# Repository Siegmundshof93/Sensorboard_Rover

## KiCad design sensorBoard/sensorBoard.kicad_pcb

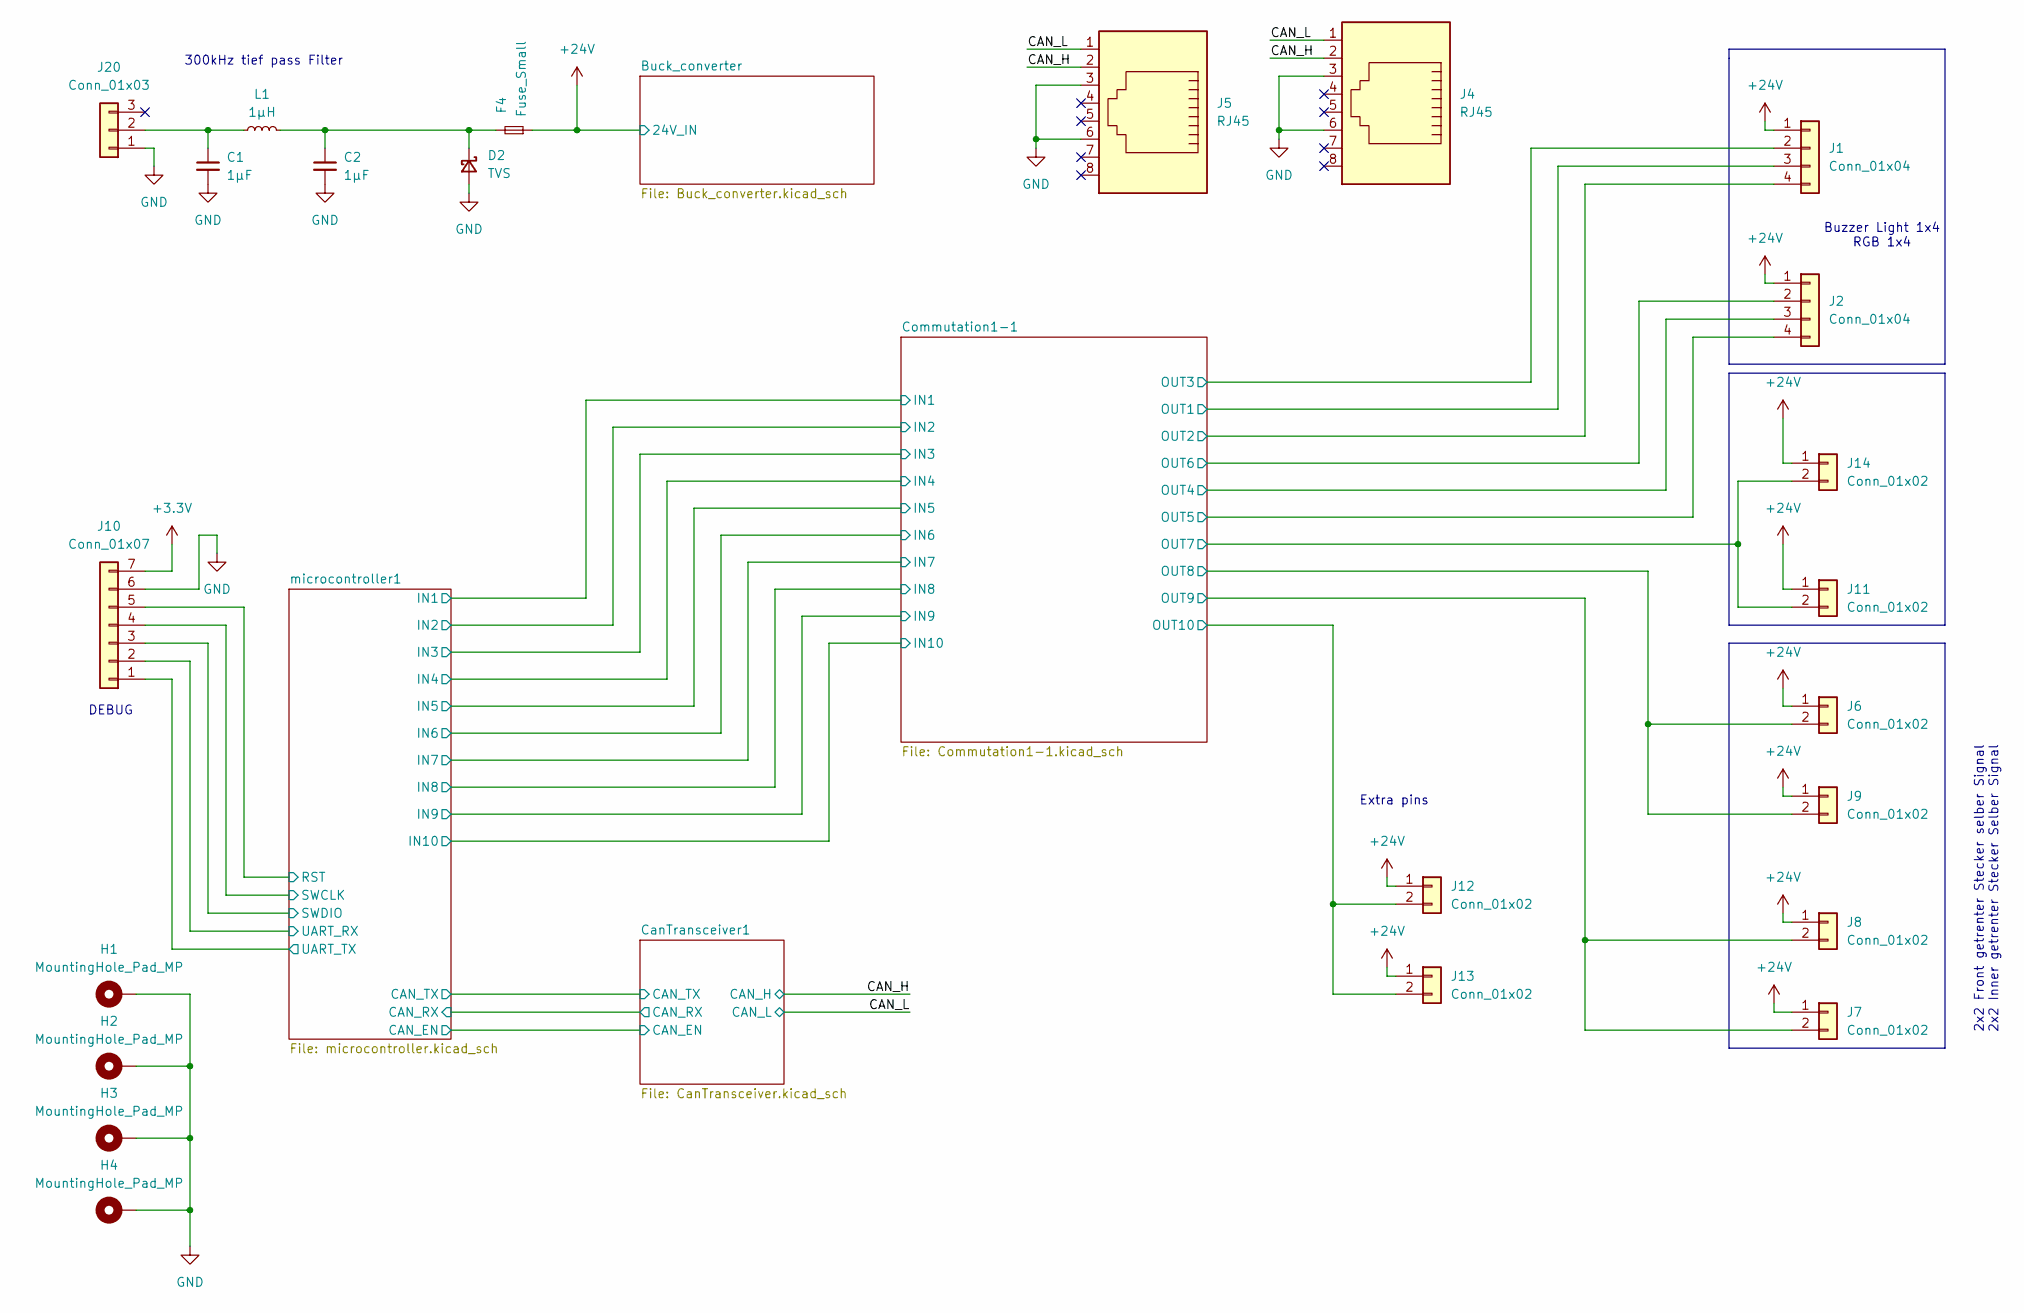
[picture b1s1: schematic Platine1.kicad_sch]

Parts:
C1, C2: 1µF; C_0603_1608Metric
D2: TVS; D_SOD-323
F4: Fuse_Small; Fuse_1206_3216Metric
H1, H2, H3, H4: MountingHole_Pad_MP; MountingHole_2.5mm_Pad_Via
J1, J2: Conn_01x04; J_Wurth_WR-MPC3_662004231722
J4, J5: RJ45; RJ45_Amphenol_RJHSE5380
J6, J7, J8, J9, J12, J13: Conn_01x02; J_Wurth_WR-MPC3_662102145021
J10: Conn_01x07; PinHeader_1x07_P2.54mm_Vertical
J11, J14: Conn_01x02; J_Wurth_WR-MPC3_662002231722
J20: Conn_01x03; Untitled
L1: 1µH; L_Wuerth_WE-PD-Typ-7345

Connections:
+3.3V: J10.7; also elsewhere on the board
+24V: F4.1, J1.1, J2.1, J6.1, J7.1, J8.1, J9.1, J11.1, J12.1, J13.1, J14.1; also elsewhere on the board
/Platine1/CAN_H: J4.2, J5.2; also elsewhere on the board
/Platine1/CAN_L: J4.1, J5.1; also elsewhere on the board
/Platine1/Commutation1-1/OUT1: J1.3; also elsewhere on the board
/Platine1/Commutation1-1/OUT2: J1.4; also elsewhere on the board
/Platine1/Commutation1-1/OUT3: J1.2; also elsewhere on the board
/Platine1/Commutation1-1/OUT4: J2.3; also elsewhere on the board
/Platine1/Commutation1-1/OUT5: J2.4; also elsewhere on the board
/Platine1/Commutation1-1/OUT6: J2.2; also elsewhere on the board
/Platine1/Commutation1-1/OUT7: J11.2, J14.2; also elsewhere on the board
/Platine1/Commutation1-1/OUT8: J6.2, J9.2; also elsewhere on the board
/Platine1/Commutation1-1/OUT9: J7.2, J8.2; also elsewhere on the board
/Platine1/Commutation1-1/OUT10: J12.2, J13.2; also elsewhere on the board
/Platine1/microcontroller1/RST: J10.5; also elsewhere on the board
/Platine1/microcontroller1/SWCLK: J10.4; also elsewhere on the board
/Platine1/microcontroller1/SWDIO: J10.3; also elsewhere on the board
/Platine1/microcontroller1/UART_RX: J10.2; also elsewhere on the board
/Platine1/microcontroller1/UART_TX: J10.1; also elsewhere on the board
GND: C1.2, C2.2, D2.2 (A), H1.MP, H2.MP, H3.MP, H4.MP, J4.3, J4.6, J5.3, J5.6, J10.6, J20.1; also elsewhere on the board
unnamed: C2.1, D2.1 (K), F4.2, L1.2
unnamed: C1.1, J20.2, L1.1

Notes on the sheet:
DEBUG
Buzzer Light 1x4 RGB 1x4
Extra pins
2x2 Front getrenter Stecker selber Signal 2x2 Inner getrenter Stecker Selber Signal
300kHz tief pass Filter

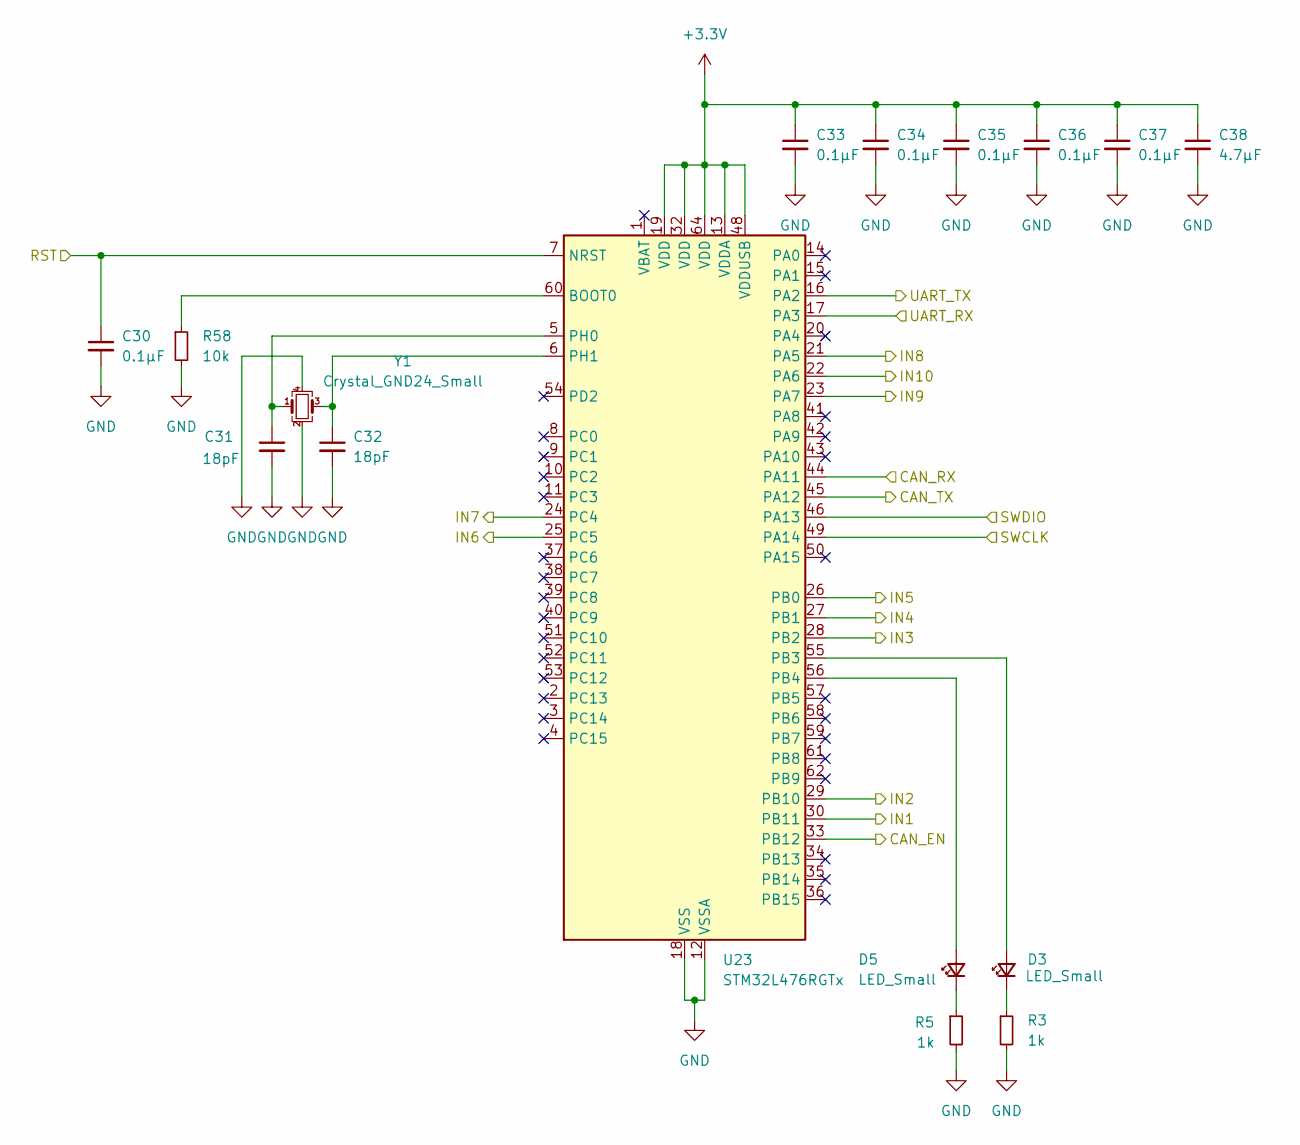
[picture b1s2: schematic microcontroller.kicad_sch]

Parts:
C30, C33, C34, C35, C36, C37: 0.1µF; C_0805_2012Metric
C31, C32: 18pF; C_0805_2012Metric
C38: 4.7µF; C_0805_2012Metric
D3, D5: LED_Small; LED_0805_2012Metric
R3, R5: 1k; R_0805_2012Metric
R58: 10k; R_0805_2012Metric
U23: STM32L476RGTx; LQFP-64_10x10mm_P0.5mm
Y1: Crystal_GND24_Small; Crystal_SMD_3225-4Pin_3.2x2.5mm

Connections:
+3.3V: C33.1, C34.1, C35.1, C36.1, C37.1, C38.1, U23.13 (VDDA), U23.19 (VDD), U23.32 (VDD), U23.48 (VDDUSB), U23.64 (VDD); also elsewhere on the board
/Platine1/CanTransceiver1/CAN_RX: U23.44 (PA11); also elsewhere on the board
/Platine1/CanTransceiver1/CAN_TX: U23.45 (PA12); also elsewhere on the board
/Platine1/Commutation1-1/IN1: U23.30 (PB11); also elsewhere on the board
/Platine1/Commutation1-1/IN2: U23.29 (PB10); also elsewhere on the board
/Platine1/Commutation1-1/IN3: U23.28 (PB2); also elsewhere on the board
/Platine1/Commutation1-1/IN4: U23.27 (PB1); also elsewhere on the board
/Platine1/Commutation1-1/IN5: U23.26 (PB0); also elsewhere on the board
/Platine1/Commutation1-1/IN6: U23.25 (PC5); also elsewhere on the board
/Platine1/Commutation1-1/IN7: U23.24 (PC4); also elsewhere on the board
/Platine1/Commutation1-1/IN8: U23.21 (PA5); also elsewhere on the board
/Platine1/Commutation1-1/IN9: U23.23 (PA7); also elsewhere on the board
/Platine1/Commutation1-1/IN10: U23.22 (PA6); also elsewhere on the board
/Platine1/microcontroller1/CAN_EN: U23.33 (PB12)
/Platine1/microcontroller1/RST: C30.1, U23.7 (NRST); also elsewhere on the board
/Platine1/microcontroller1/SWCLK: U23.49 (PA14); also elsewhere on the board
/Platine1/microcontroller1/SWDIO: U23.46 (PA13); also elsewhere on the board
/Platine1/microcontroller1/UART_RX: U23.17 (PA3); also elsewhere on the board
/Platine1/microcontroller1/UART_TX: U23.16 (PA2); also elsewhere on the board
GND: C30.2, C31.2, C32.2, C33.2, C34.2, C35.2, C36.2, C37.2, C38.2, R3.2, R5.2, R58.2, U23.12 (VSSA), U23.18 (VSS), U23.31 (VSS), U23.47 (VSS), U23.63 (VSS), Y1.2, Y1.4; also elsewhere on the board
unnamed: D3.2 (A), U23.55 (PB3)
unnamed: D3.1 (K), R3.1
unnamed: D5.2 (A), U23.56 (PB4)
unnamed: D5.1 (K), R5.1
unnamed: R58.1, U23.60 (BOOT0)
unnamed: C31.1, U23.5 (PH0), Y1.1
unnamed: C32.1, U23.6 (PH1), Y1.3

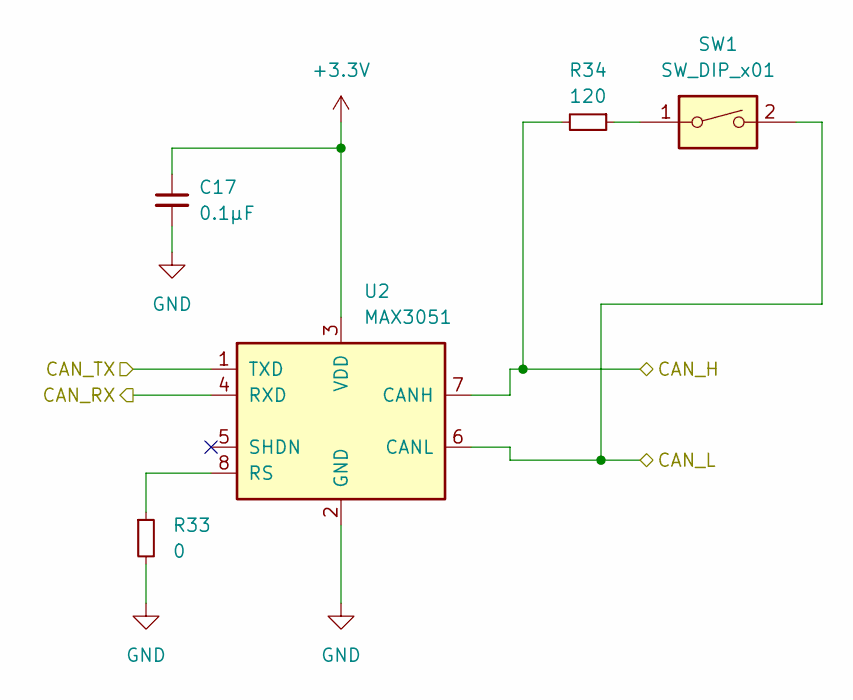
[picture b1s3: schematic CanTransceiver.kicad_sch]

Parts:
C17: 0.1µF; C_0805_2012Metric
R33: 0; R_0805_2012Metric
R34: 120; R_0805_2012Metric
SW1: SW_DIP_x01; 416131160801
U2: MAX3051; SOIC-8_3.9x4.9mm_P1.27mm

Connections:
+3.3V: C17.1, U2.3 (VDD); also elsewhere on the board
/Platine1/CAN_H: R34.2, U2.7 (CANH); also elsewhere on the board
/Platine1/CAN_L: SW1.2, U2.6 (CANL); also elsewhere on the board
/Platine1/CanTransceiver1/CAN_RX: U2.4 (RXD); also elsewhere on the board
/Platine1/CanTransceiver1/CAN_TX: U2.1 (TXD); also elsewhere on the board
GND: C17.2, R33.2, U2.2 (GND); also elsewhere on the board
unnamed: R34.1, SW1.1
unnamed: R33.1, U2.8 (RS)

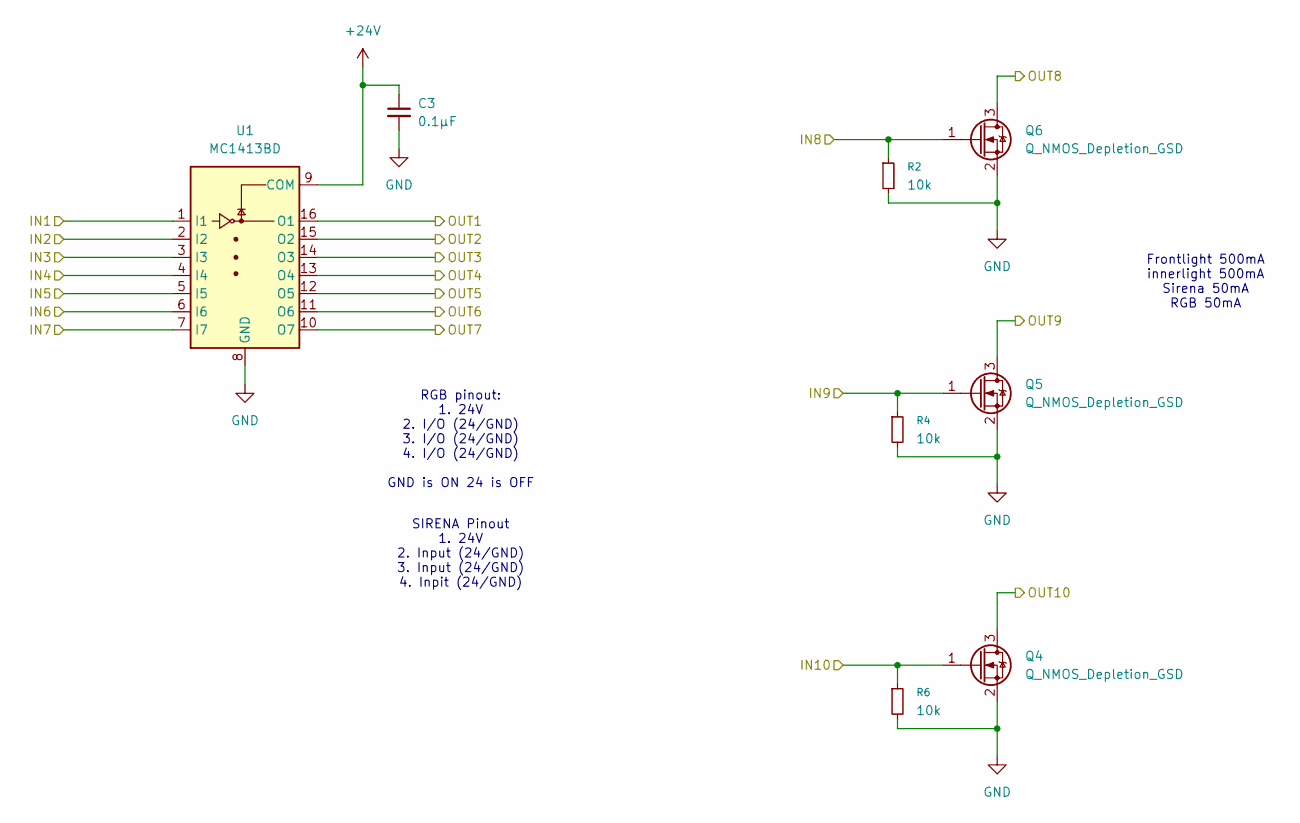
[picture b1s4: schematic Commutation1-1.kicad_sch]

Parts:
C3: 0.1µF; C_0603_1608Metric
Q4, Q5, Q6: Q_NMOS_Depletion_GSD; SOT-23
R2, R4, R6: 10k; R_0805_2012Metric
U1: MC1413BD; SOIC-16_3.9x9.9mm_P1.27mm

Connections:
+24V: C3.1, U1.9 (COM); also elsewhere on the board
/Platine1/Commutation1-1/IN1: U1.1 (I1); also elsewhere on the board
/Platine1/Commutation1-1/IN2: U1.2 (I2); also elsewhere on the board
/Platine1/Commutation1-1/IN3: U1.3 (I3); also elsewhere on the board
/Platine1/Commutation1-1/IN4: U1.4 (I4); also elsewhere on the board
/Platine1/Commutation1-1/IN5: U1.5 (I5); also elsewhere on the board
/Platine1/Commutation1-1/IN6: U1.6 (I6); also elsewhere on the board
/Platine1/Commutation1-1/IN7: U1.7 (I7); also elsewhere on the board
/Platine1/Commutation1-1/IN8: Q6.1 (G), R2.1; also elsewhere on the board
/Platine1/Commutation1-1/IN9: Q5.1 (G), R4.1; also elsewhere on the board
/Platine1/Commutation1-1/IN10: Q4.1 (G), R6.1; also elsewhere on the board
/Platine1/Commutation1-1/OUT1: U1.16 (O1); also elsewhere on the board
/Platine1/Commutation1-1/OUT2: U1.15 (O2); also elsewhere on the board
/Platine1/Commutation1-1/OUT3: U1.14 (O3); also elsewhere on the board
/Platine1/Commutation1-1/OUT4: U1.13 (O4); also elsewhere on the board
/Platine1/Commutation1-1/OUT5: U1.12 (O5); also elsewhere on the board
/Platine1/Commutation1-1/OUT6: U1.11 (O6); also elsewhere on the board
/Platine1/Commutation1-1/OUT7: U1.10 (O7); also elsewhere on the board
/Platine1/Commutation1-1/OUT8: Q6.3 (D); also elsewhere on the board
/Platine1/Commutation1-1/OUT9: Q5.3 (D); also elsewhere on the board
/Platine1/Commutation1-1/OUT10: Q4.3 (D); also elsewhere on the board
GND: C3.2, Q4.2 (S), Q5.2 (S), Q6.2 (S), R2.2, R4.2, R6.2, U1.8 (GND); also elsewhere on the board

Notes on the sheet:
RGB pinout: 1. 24V 2. I/O (24/GND) 3. I/O (24/GND) 4. I/O (24/GND) GND is ON 24 is OFF
SIRENA Pinout 1. 24V 2. Input (24/GND) 3. Input (24/GND) 4. Inpit (24/GND)
Frontlight 500mA innerlight 500mA Sirena 50mA RGB 50mA

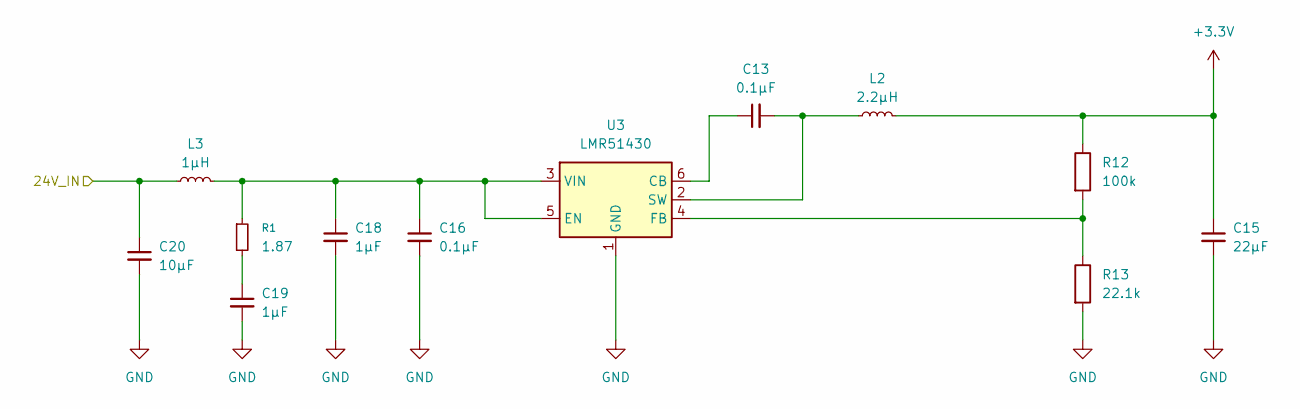
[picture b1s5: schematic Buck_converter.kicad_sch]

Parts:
C13: 0.1µF; C_0402_1005Metric
C15: 22µF; CP_Elec_6.3x5.8
C16: 0.1µF; C_0603_1608Metric
C18, C19: 1µF; C_0603_1608Metric
C20: 10µF; C_0603_1608Metric
L2: 2.2µH; L_Wuerth_WE-PD-Typ-7345
L3: 1µH; L_Wuerth_WE-PD-Typ-7345
R1: 1.87; R_0805_2012Metric
R12: 100k; R_0805_2012Metric
R13: 22.1k; R_0805_2012Metric
U3: LMR51430; SOT-23-6

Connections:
+3.3V: C15.1, L2.2, R12.1; also elsewhere on the board
+24V: C20.1, L3.1; also elsewhere on the board
GND: C15.2, C16.2, C18.2, C19.2, C20.2, R13.2, U3.1 (GND); also elsewhere on the board
unnamed: C19.1, R1.2
unnamed: C13.1, U3.6 (CB)
unnamed: C16.1, C18.1, L3.2, R1.1, U3.3 (VIN), U3.5 (EN)
unnamed: R12.2, R13.1, U3.4 (FB)
unnamed: C13.2, L2.1, U3.2 (SW)

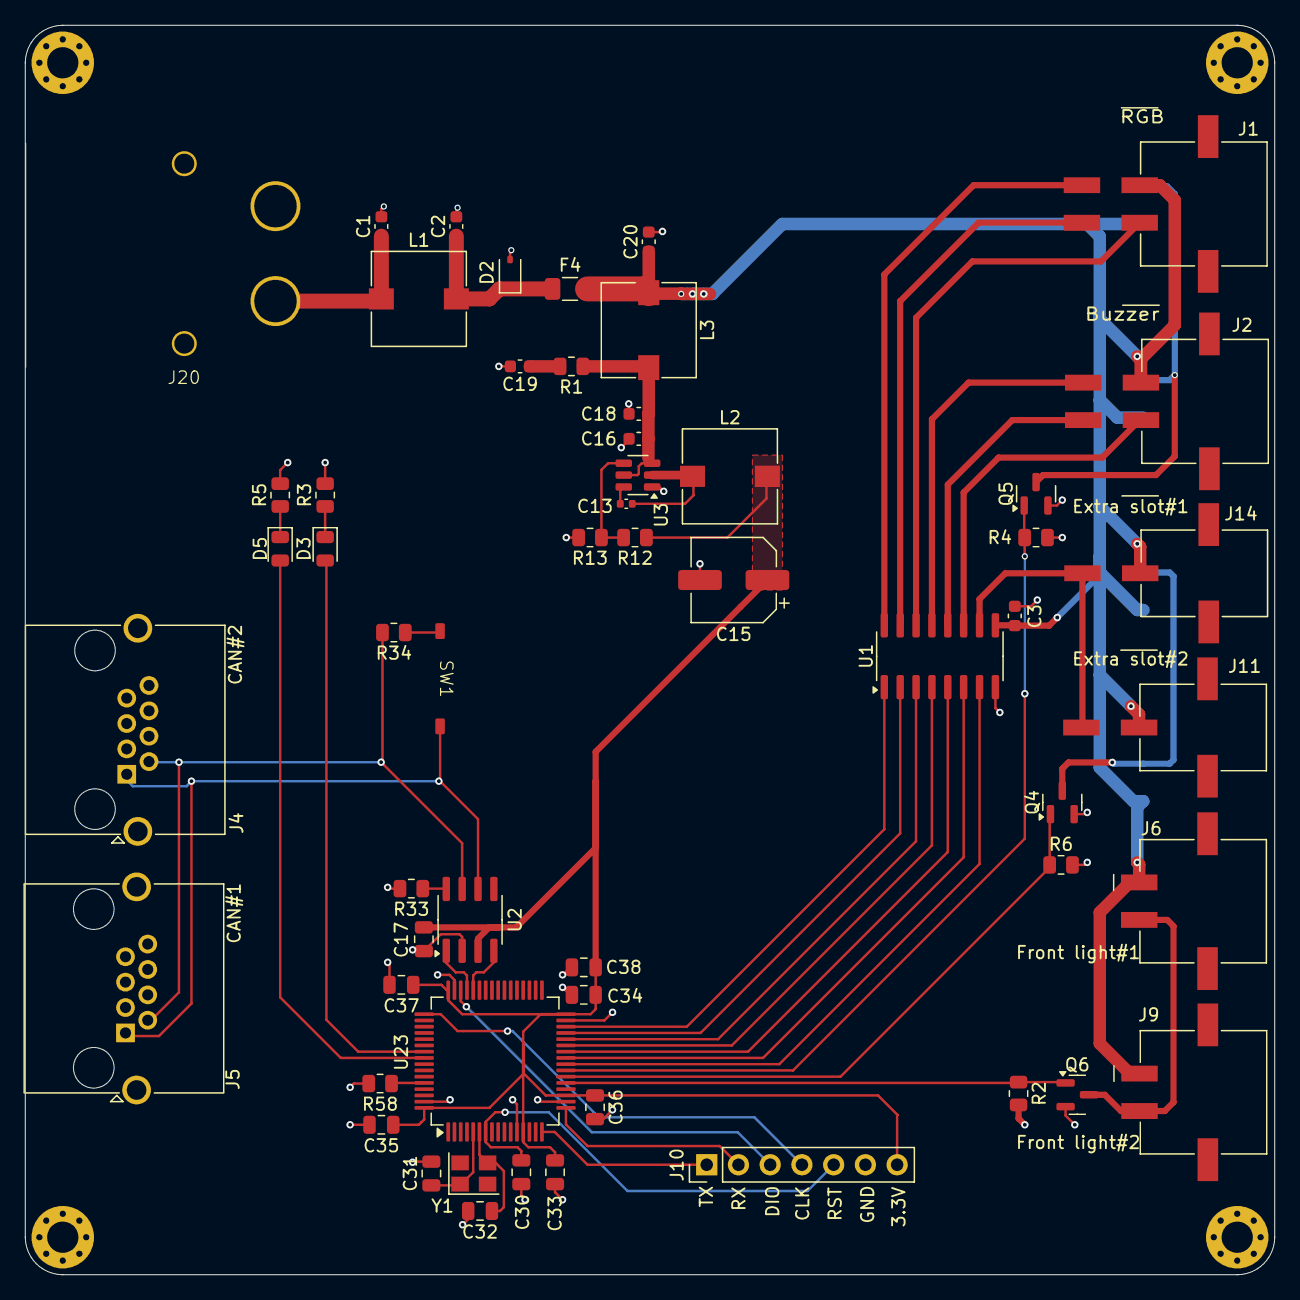
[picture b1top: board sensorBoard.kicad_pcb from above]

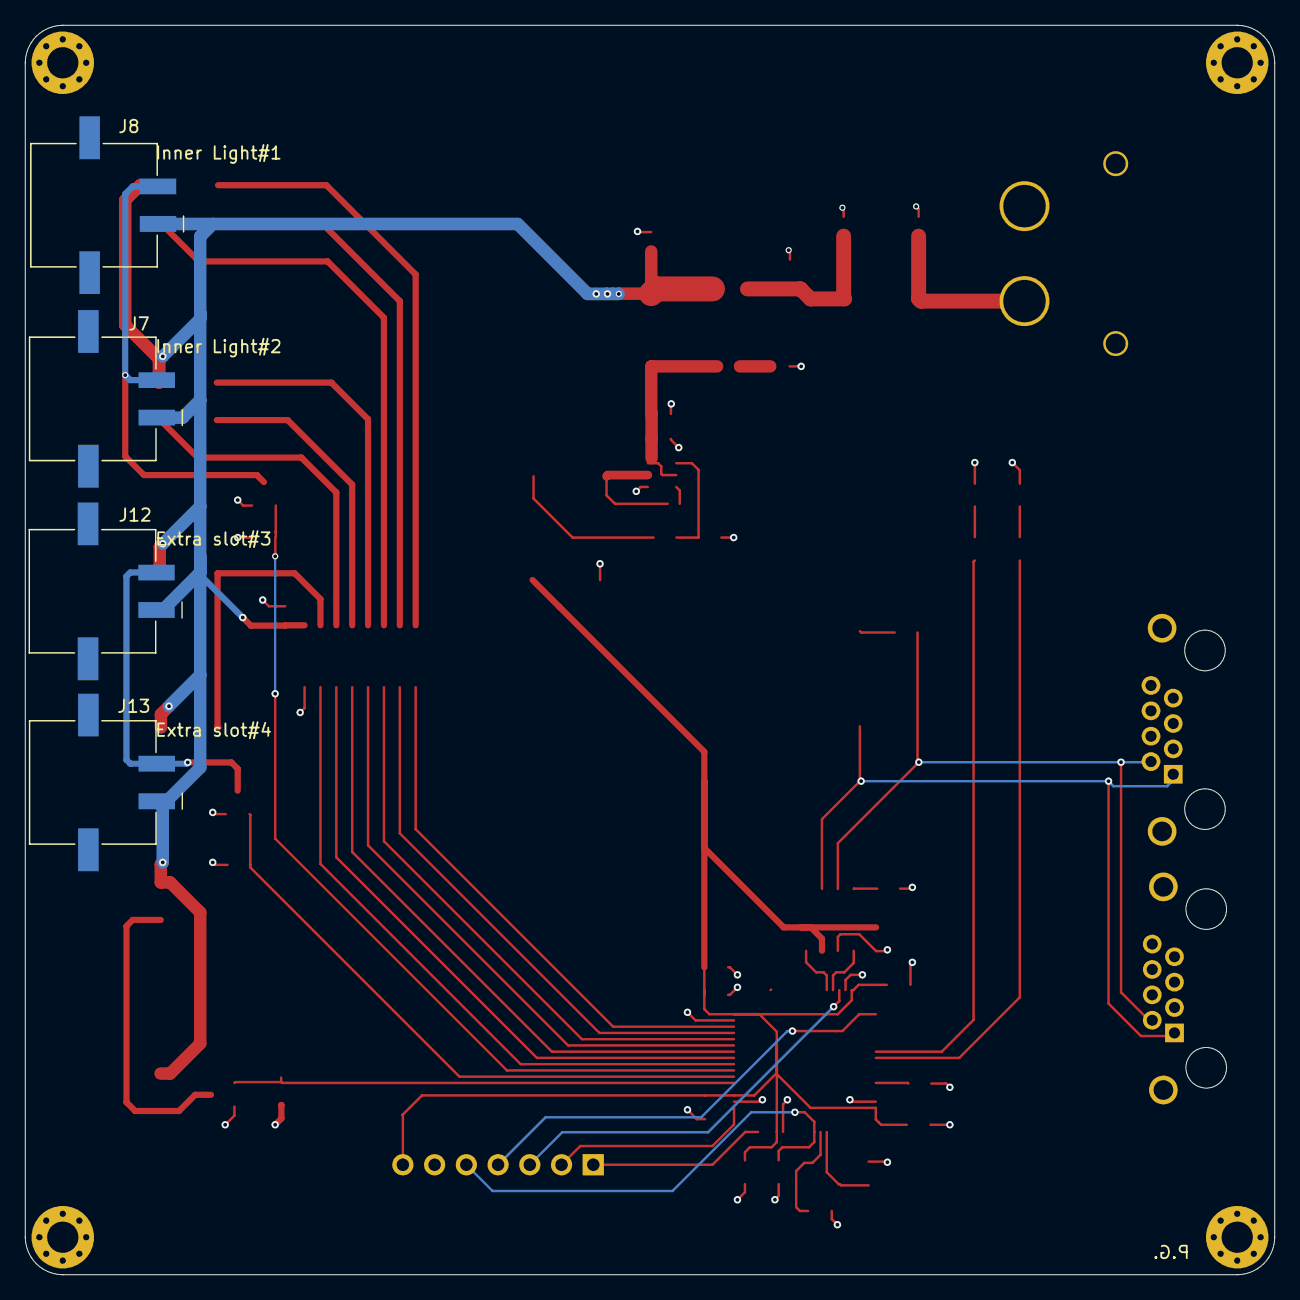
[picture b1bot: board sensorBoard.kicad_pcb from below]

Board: 4 copper layers, 100.0 x 100.0 mm, 64 parts (4 on the bottom side), 48 nets.

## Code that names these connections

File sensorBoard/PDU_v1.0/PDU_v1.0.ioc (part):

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Mcu.Name=STM32L476R(C-E-G)Tx
Mcu.Package=LQFP64
Mcu.UserName=STM32L476RGTx
PA11.Mode=CAN_Activate
PA11.Signal=CAN1_RX
PA12.Mode=CAN_Activate
PA12.Signal=CAN1_TX
PA13\ (JTMS-SWDIO).Mode=Serial_Wire
PA13\ (JTMS-SWDIO).Signal=SYS_JTMS-SWDIO
PA14\ (JTCK-SWCLK).Mode=Serial_Wire
PA14\ (JTCK-SWCLK).Signal=SYS_JTCK-SWCLK
PA2.Mode=Asynchronous
PA2.Signal=USART2_TX
PA3.Mode=Asynchronous
PA3.Signal=USART2_RX
PA5.Signal=GPIO_Output
PA6.Signal=GPIO_Output
PA7.Signal=GPIO_Output
PB0.Signal=GPIO_Output
PB1.Signal=GPIO_Output
PB10.Signal=GPIO_Output
PB11.Signal=GPIO_Output
PB2.Signal=GPIO_Output
PC4.Signal=GPIO_Output
PC5.Signal=GPIO_Output
RCC.HSE_VALUE=8000000
RCC.SYSCLKFreq_VALUE=80000000
RCC.SYSCLKSource=RCC_SYSCLKSOURCE_PLLCLK
board=custom

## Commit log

2024-10-01 new Project
2024-10-04 added the footprints, connectors left
2024-10-07 started the layout
2024-10-09 started to connect layout. added 0 Ohm resistors to separate the drivers.
2024-10-11 Die Platine mit den allen Komponenten auf einziges PCB
2024-10-11 new two separate pcbs
2024-10-12 Das erstes PCB ist fast fertig. Die Vias waren auf die Platine platziert und Poligon war gefüllt.
2024-10-12 das erstes PCB ist fertig. Lightsensor check.
2024-10-14 Die zweite Leiterplatte ist fast fertig.
2024-10-16 logo fällt
2024-10-17 logo und Signature wurden hinzufügt
2024-10-18 finisched PCB
2024-10-29 aktualisierte Platine mit verschiedenen Stecker
2025-09-21 added old software + new PCB
